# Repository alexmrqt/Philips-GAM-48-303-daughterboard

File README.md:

# Philips GAM 48-303 fix

## Presentation
I am, since many years, the proud owner of a Philips GAM 48-303 soldering station.
This is an old piece of hardware, that works well nonetheless, and can even drive a brand new Hakko 907.

On the inside, it is only based around four main components:
 - A mains transformer that step down 230V AC to 24V AC,
 - A TIC225A triac to deliver (or not) power to the iron,
 - A CA3140 op-amp to compute an error signal from the temperature set point and the iron temperature,
 - A U106BS "monolithic integrated zero voltage", which is used to drive the triac (TIC225A) based on the error signal computed by the CA3140A op-amp (proportional controller).

Of these four components, the TIC225A triac and the U106BS are not produced any more. Finding a pin-compatible replacement for the TIC225A triac is easy, but none are available for the U106BS.

Unfortunately for me, the latter component ended up faulty in my soldering station. Thus, this project provides a KiCAD project for a daughter board that can be easily mounted on top of the existing board in the Philips GAM 48-303, and provide the features of the U106BS.

This daughter board is based on a UAA2016 "zero voltage switch power controller" and an additional CA3140 (to replace the internal op amp of the U106BS, any other op amp should do the job, by the way).

## Repository layout
This repository is organized as follows:
 - docs/ contains datasheet for the various components used in the project, as well as pictured of the original PCB present in the soldering station.
 - soldering-station-hat/ is a KiCAD project containing all the files to create and modify the daughter board.

 - soldering-station-pcb/ is a KiCAD project used for reverse-engineering purposes. Its schematics draws components and connection over a picture of the PCB.
 - soldering-station/ is a KiCAD project used for reverse-engineering purposes. Its schematics splits the original circuits into functional units. It also contains the way the UAA2016 and CA3140 should be connected with the original board.

## Final thoughts
Overall, after calibrating the circuit using the potentiometer of the error amplifier, this circuit works like a charm!

Be aware that I realized the circuit on a proto-board, and never had the occasion to make the PCB present in soldering-station-hat/ fabricated. Thus, it may or may not fit properly on top of the original circuit.

Finally, if I had to make a v2 of this project, I would add the necessary circuitry to adjust the hysteresis off the UAA2016, because the soldering station switch ON and OFF a bit too often for my taste.

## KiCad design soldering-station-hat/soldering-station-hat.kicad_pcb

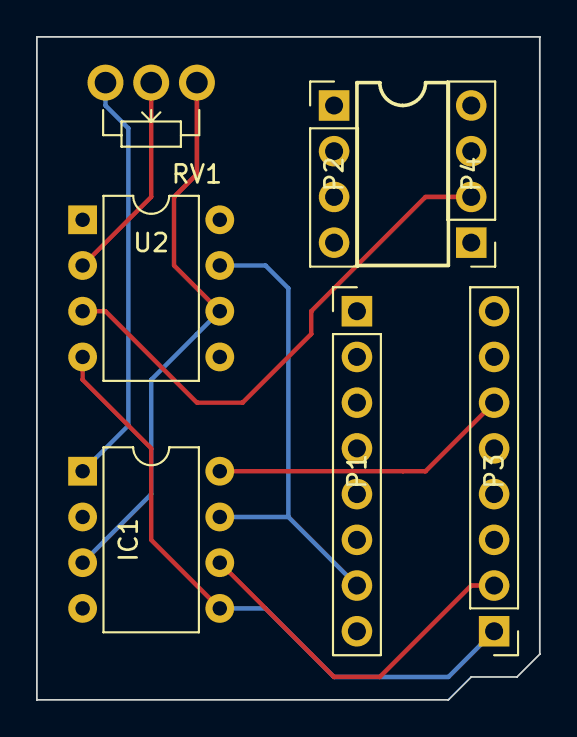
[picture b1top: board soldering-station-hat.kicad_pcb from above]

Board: 2 copper layers, 27.9 x 36.8 mm, 7 parts (0 on the bottom side), 8 nets.

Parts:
IC1: UAA2016PG; DIP-8_W7.62mm
P1, P3: CONN_01X08; Pin_Header_Straight_1x08_Pitch2.54mm
P2, P4: CONN_01X04; Pin_Header_Straight_1x04_Pitch2.54mm
RV1: 200k; Potentiometer_WirePads_Small
U2: CA3140; DIP-8_W7.62mm

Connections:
/CA3140_6: P4.2, U2.3
/Temp_error_amp: IC1.3, RV1.1, U2.6
/U106BS_7: IC1.7, P1.7, U2.7
/U106BS_9: IC1.5, P3.1, U2.4
/U106BS_10: IC1.6, P3.2
/U106BS_14: IC1.8, P3.6
/Vref: IC1.1, RV1.3
unnamed: RV1.2, U2.2

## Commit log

2019-01-21 Add a gitignore for kicad projects.
2019-01-21 Add project files and README.
2019-01-21 Removes unused file.
2019-01-21 Add an image of the PCB in the README.
